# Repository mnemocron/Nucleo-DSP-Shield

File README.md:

# Nucleo-DSP-Shield
Audio DSP Shield for STM32 Nucleo-144 Boards (H723zg) based on the TLV320 CODEC

---

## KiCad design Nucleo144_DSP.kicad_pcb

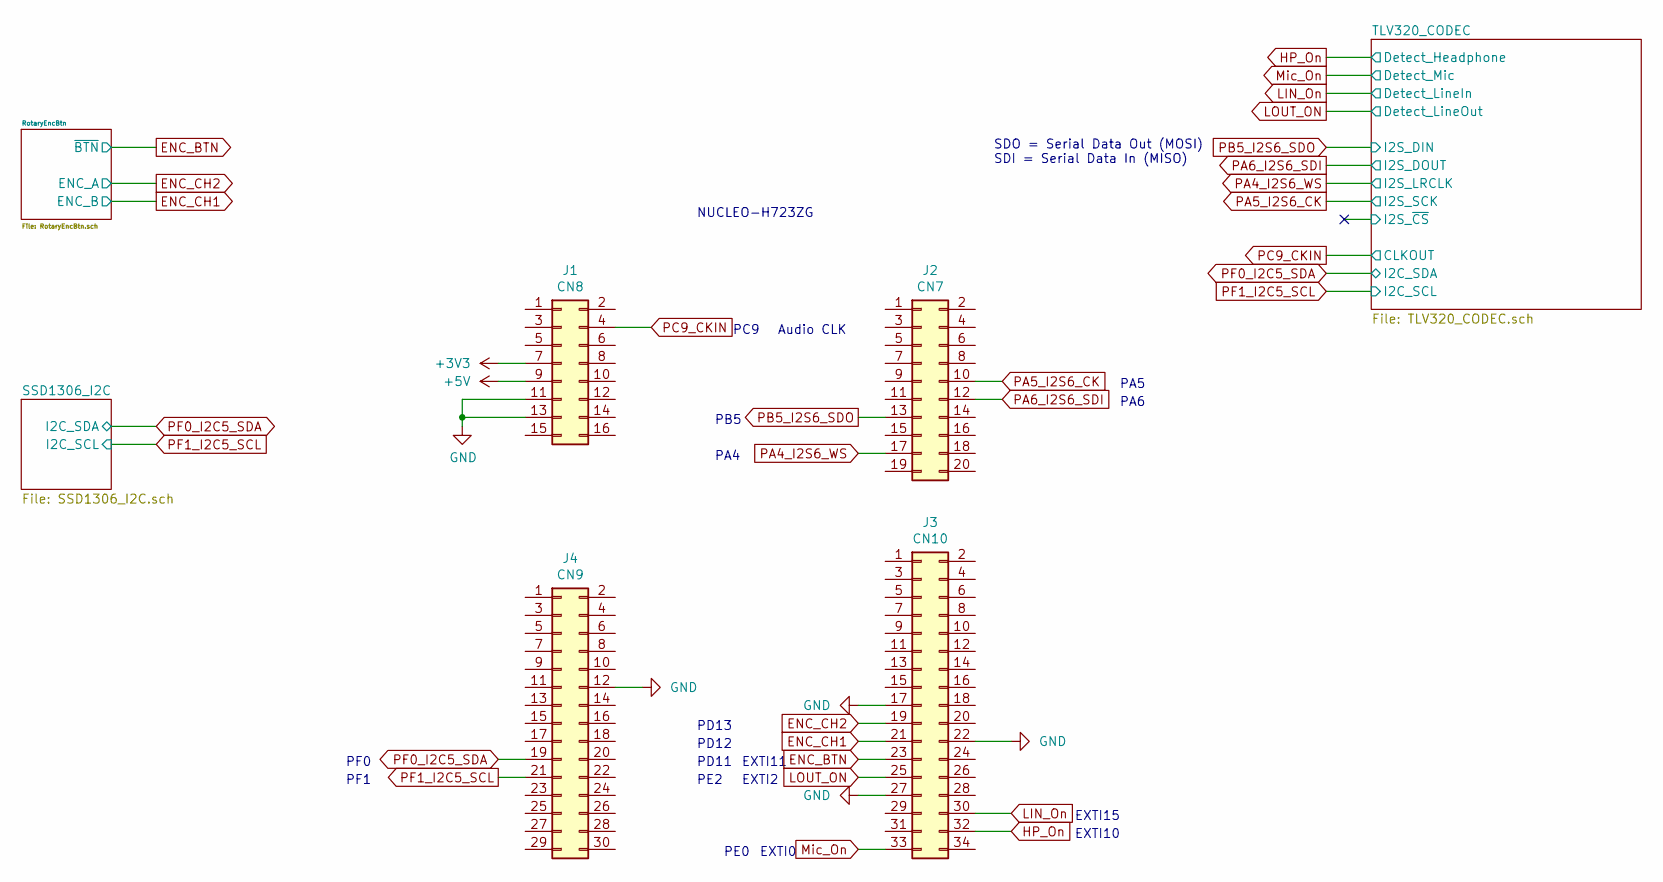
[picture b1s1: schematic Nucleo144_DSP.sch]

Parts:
J1: CN8; PinSocket_2x08_P2.54mm_Vertical; JLCPCB do not place
J2: CN7; PinSocket_2x10_P2.54mm_Vertical; JLCPCB do not place
J3: CN10; PinSocket_2x17_P2.54mm_Vertical; JLCPCB do not place
J4: CN9; PinSocket_2x15_P2.54mm_Vertical; JLCPCB do not place

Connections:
+5V: J1.9
ENC_BTN: J3.23; also elsewhere on the board
ENC_CH1: J3.21; also elsewhere on the board
ENC_CH2: J3.19; also elsewhere on the board
GND: J1.11, J1.13, J3.17, J3.22, J3.27, J4.12; also elsewhere on the board
HP_On: J3.32; also elsewhere on the board
LIN_On: J3.30; also elsewhere on the board
LOUT_ON: J3.25; also elsewhere on the board
Mic_On: J3.33; also elsewhere on the board
PA4_I2S6_WS: J2.17; also elsewhere on the board
PA5_I2S6_CK: J2.10; also elsewhere on the board
PA6_I2S6_SDI: J2.12; also elsewhere on the board
PB5_I2S6_SDO: J2.13; also elsewhere on the board
PC9_CKIN: J1.4; also elsewhere on the board
PF0_I2C5_SDA: J4.19; also elsewhere on the board
PF1_I2C5_SCL: J4.21; also elsewhere on the board

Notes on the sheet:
NUCLEO-H723ZG
EXTI0
EXTI10
EXTI11
EXTI2
EXTI15
PE0
PE2
PD11
PD12
PD13
PA4
PB5
PA6
PA5
SDO = Serial Data Out (MOSI) SDI = Serial Data In (MISO)
PF1
PF0
PC9
Audio CLK

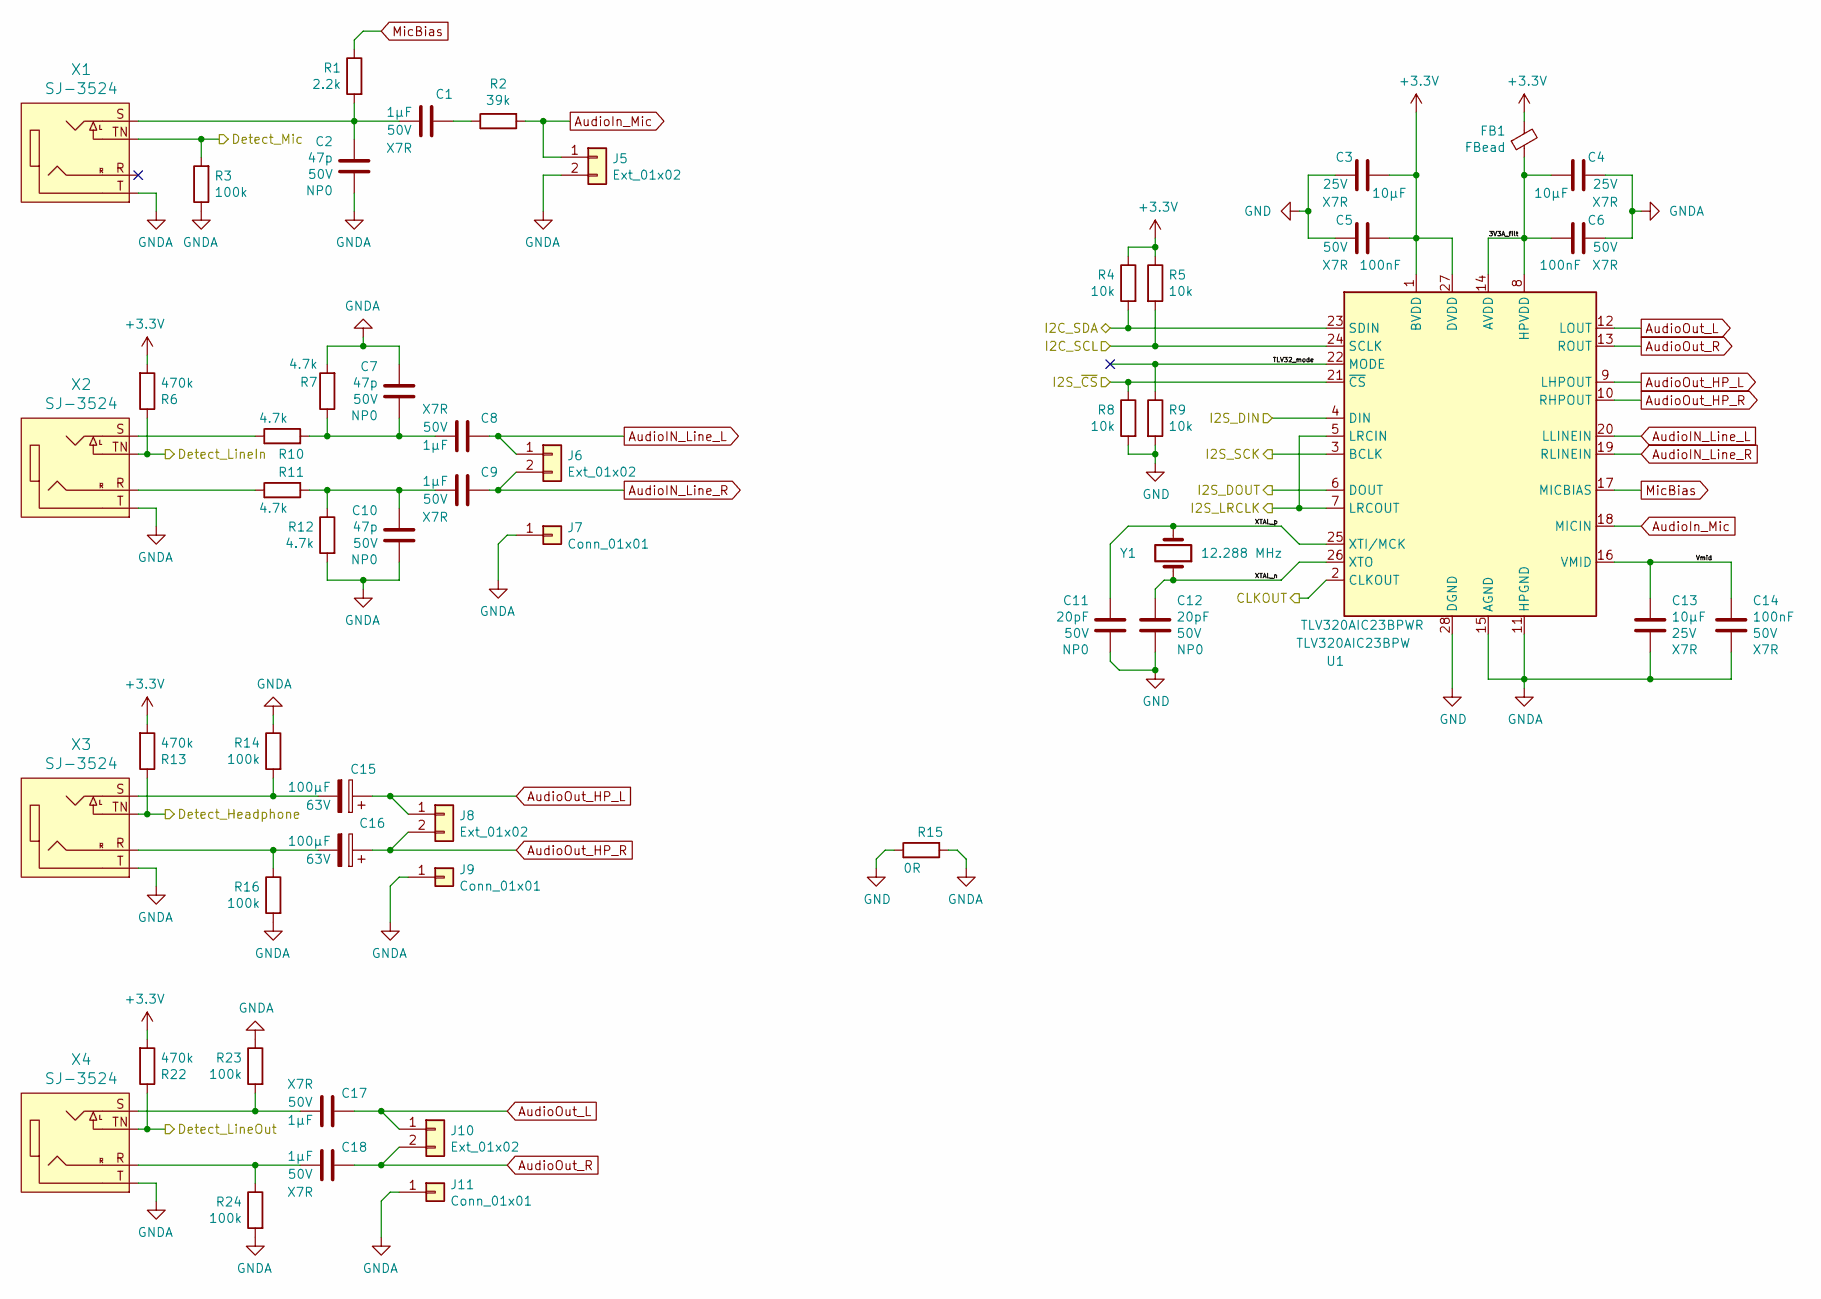
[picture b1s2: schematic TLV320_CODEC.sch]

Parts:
C1, C8, C9, C17, C18: 1μF; C_0805_2012Metric; Voltage 50V; JLCPCB Basic Part
C2, C7, C10: 47p; C_0805_2012Metric; Voltage 50V; JLCPCB Basic Part
C3, C4, C13: 10μF; C_0805_2012Metric; Voltage 25V; JLCPCB Basic Part
C5, C6, C14: 100nF; C_0805_2012Metric; Voltage 50V; JLCPCB Basic Part
C11, C12: 20pF; C_0805_2012Metric; Voltage 50V; JLCPCB Basic Part
C15, C16: 100μF; CP_Radial_D10.0mm_P5.00mm; Voltage 63V; JLCPCB do not place
FB1: FBead; R_0805_2012Metric; JLCPCB do not place
J5, J6, J8, J10: Ext_01x02; PinSocket_1x02_P2.54mm_Vertical; JLCPCB do not place
J7, J9, J11: Conn_01x01; PinSocket_1x01_P2.54mm_Vertical; JLCPCB do not place
R1: 2.2k; R_0805; Tolerance 1%; JLCPCB Basic Part
R2: 39k; R_0805; Tolerance 1%; JLCPCB Basic Part
R3, R14, R16, R23, R24: 100k; R_0805; Tolerance 1%; JLCPCB Basic Part
R4, R5, R8, R9: 10k; R_0805; Tolerance 1%; JLCPCB Basic Part
R6, R13, R22: 470k; R_0805; Tolerance 1%; JLCPCB Basic Part
R7, R10, R11, R12: 4.7k; R_0805; Tolerance 1%; JLCPCB Basic Part
R15: 0R; R_0805; Tolerance 1%; JLCPCB Basic Part
U1: TLV320AIC23BPW; TSSOP-28_4.4x9.7mm_P0.65mm; JLCPCB Extended Part
X1, X2, X3, X4: SJ-3524; Jack_3.5mm_CUI_SJ-3524-SMT_Horizontal; JLCPCB do not place
Y1: 12.288 MHz; Crystal_SMD_HC49-SD; JLCPCB Extended Part

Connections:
/TLV320_CODEC/3V3A_filt: C4.2, C6.2, FB1.1, U1.8 (HPVDD), U1.14 (AVDD)
/TLV320_CODEC/I2S_~CS~: R8.1, U1.21 (~CS~)
/TLV320_CODEC/TLV32_mode: R9.1, U1.22 (MODE)
/TLV320_CODEC/Vmid: C13.1, C14.1, U1.16 (VMID)
/TLV320_CODEC/XTAL_n: C12.2, U1.26 (XTO), Y1.1
/TLV320_CODEC/XTAL_p: C11.2, U1.25 (XTI/MCK), Y1.2
AudioIN_Line_L: C8.2, J6.1, U1.20 (LLINEIN)
AudioIN_Line_R: C9.2, J6.2, U1.19 (RLINEIN)
AudioIn_Mic: J5.1, R2.2, U1.18 (MICIN)
AudioOut_HP_L: C15.1, J8.1, U1.9 (LHPOUT)
AudioOut_HP_R: C16.1, J8.2, U1.10 (RHPOUT)
AudioOut_L: C17.2, J10.1, U1.12 (LOUT)
AudioOut_R: C18.2, J10.2, U1.13 (ROUT)
GND: C3.1, C5.1, C11.1, C12.1, R8.2, R9.2, R15.1, U1.28 (DGND); also elsewhere on the board
GNDA: C2.2, C4.1, C6.1, C7.1, C10.2, C13.2, C14.2, J5.2, J7.1, J9.1, J11.1, R3.1, R7.2, R12.2, R14.1, R15.2, R16.2, R23.1, R24.2, U1.11 (HPGND), U1.15 (AGND), X1.T, X2.T, X3.T, X4.T
HP_On: R13.1, X3.TN; also elsewhere on the board
LIN_On: R6.1, X2.TN; also elsewhere on the board
LOUT_ON: R22.1, X4.TN; also elsewhere on the board
MicBias: R1.1, U1.17 (MICBIAS)
Mic_On: R3.2, X1.TN; also elsewhere on the board
unnamed: C1.1, C2.1, R1.2, X1.S
unnamed: C1.2, R2.1
unnamed: C7.2, C8.1, R7.1, R10.2
unnamed: C9.1, C10.1, R11.2, R12.1
unnamed: C15.2, R14.2, X3.S
unnamed: C16.2, R16.1, X3.R
unnamed: C17.1, R23.2, X4.S
unnamed: C18.1, R24.1, X4.R
unnamed: R10.1, X2.S
unnamed: R11.1, X2.R
PA4_I2S6_WS: U1.5 (LRCIN), U1.7 (LRCOUT); also elsewhere on the board
PA5_I2S6_CK: U1.3 (BCLK); also elsewhere on the board
PA6_I2S6_SDI: U1.6 (DOUT); also elsewhere on the board
PB5_I2S6_SDO: U1.4 (DIN); also elsewhere on the board
PC9_CKIN: U1.2 (CLKOUT); also elsewhere on the board
PF0_I2C5_SDA: R4.2, U1.23 (SDIN); also elsewhere on the board
PF1_I2C5_SCL: R5.2, U1.24 (SCLK); also elsewhere on the board

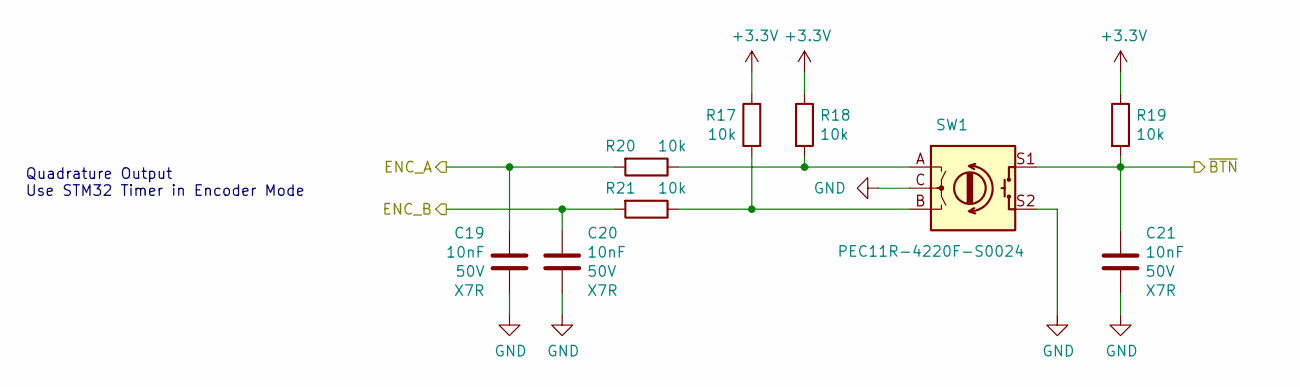
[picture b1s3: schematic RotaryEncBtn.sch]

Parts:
C19, C20, C21: 10nF; C_0805_2012Metric; Voltage 50V; JLCPCB Basic Part
R17, R18, R19, R20, R21: 10k; R_0805; Tolerance 1%; JLCPCB Basic Part
SW1: PEC11R-4220F-S0024; RotaryEncoder_Alps_EC11E-Switch_Vertical_H20mm_CircularMoun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; JLCPCB do not place

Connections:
ENC_BTN: C21.1, R19.2, SW1.S1; also elsewhere on the board
ENC_CH1: C20.1, R21.2; also elsewhere on the board
ENC_CH2: C19.2, R20.2; also elsewhere on the board
GND: C19.1, C20.2, C21.2, SW1.C, SW1.S2; also elsewhere on the board
unnamed: R17.2, R21.1, SW1.B
unnamed: R18.2, R20.1, SW1.A

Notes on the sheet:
Quadrature Output Use STM32 Timer in Encoder Mode

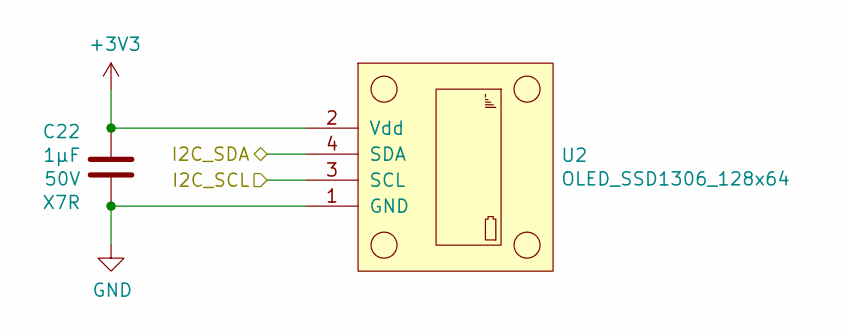
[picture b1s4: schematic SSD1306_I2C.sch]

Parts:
C22: 1μF; C_0805_2012Metric; Voltage 50V; JLCPCB Basic Part
U2: OLED_SSD1306_128x64; PinSocket_1x04_P2.54mm_Vertical; JLCPCB do not place

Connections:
GND: C22.1, U2.1 (GND); also elsewhere on the board
PF0_I2C5_SDA: U2.4 (SDA); also elsewhere on the board
PF1_I2C5_SCL: U2.3 (SCL); also elsewhere on the board

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
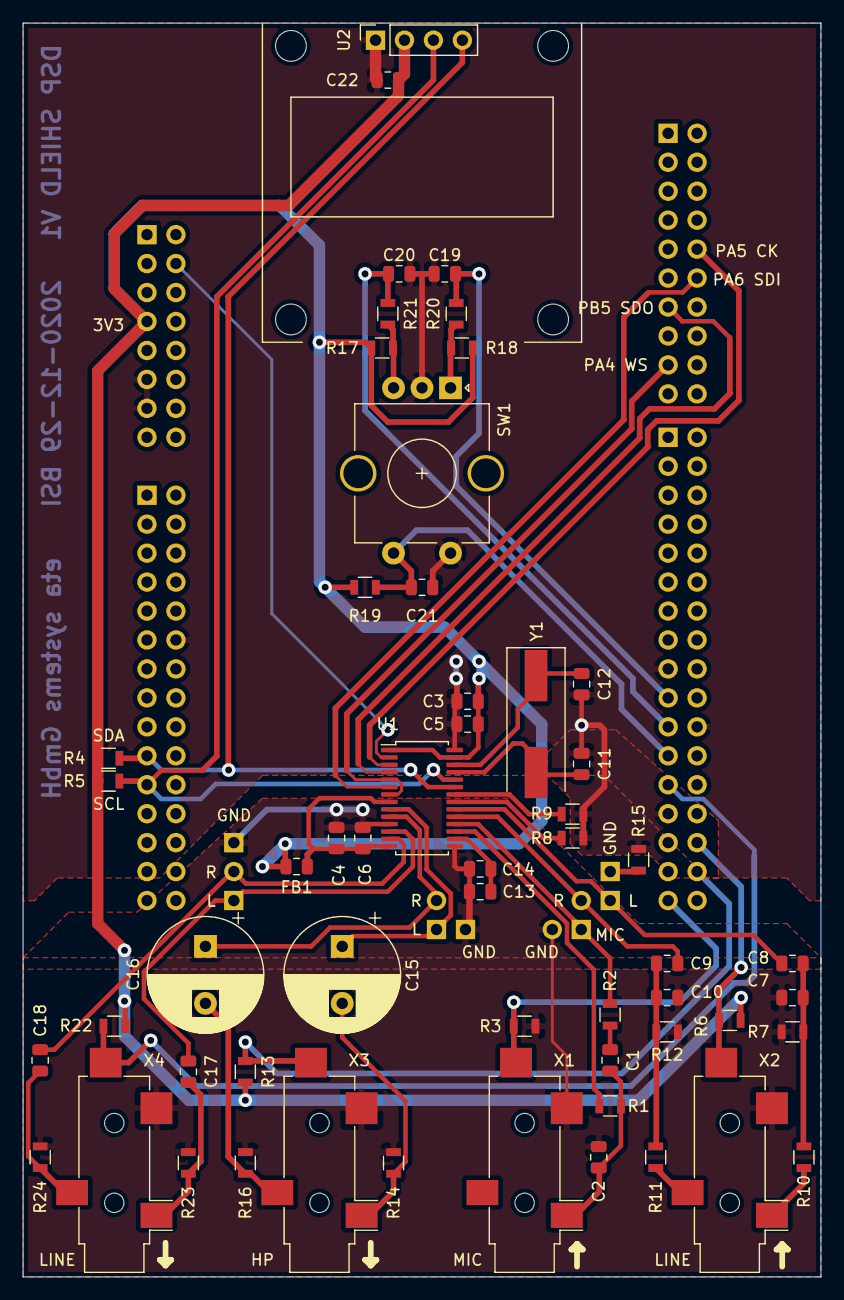
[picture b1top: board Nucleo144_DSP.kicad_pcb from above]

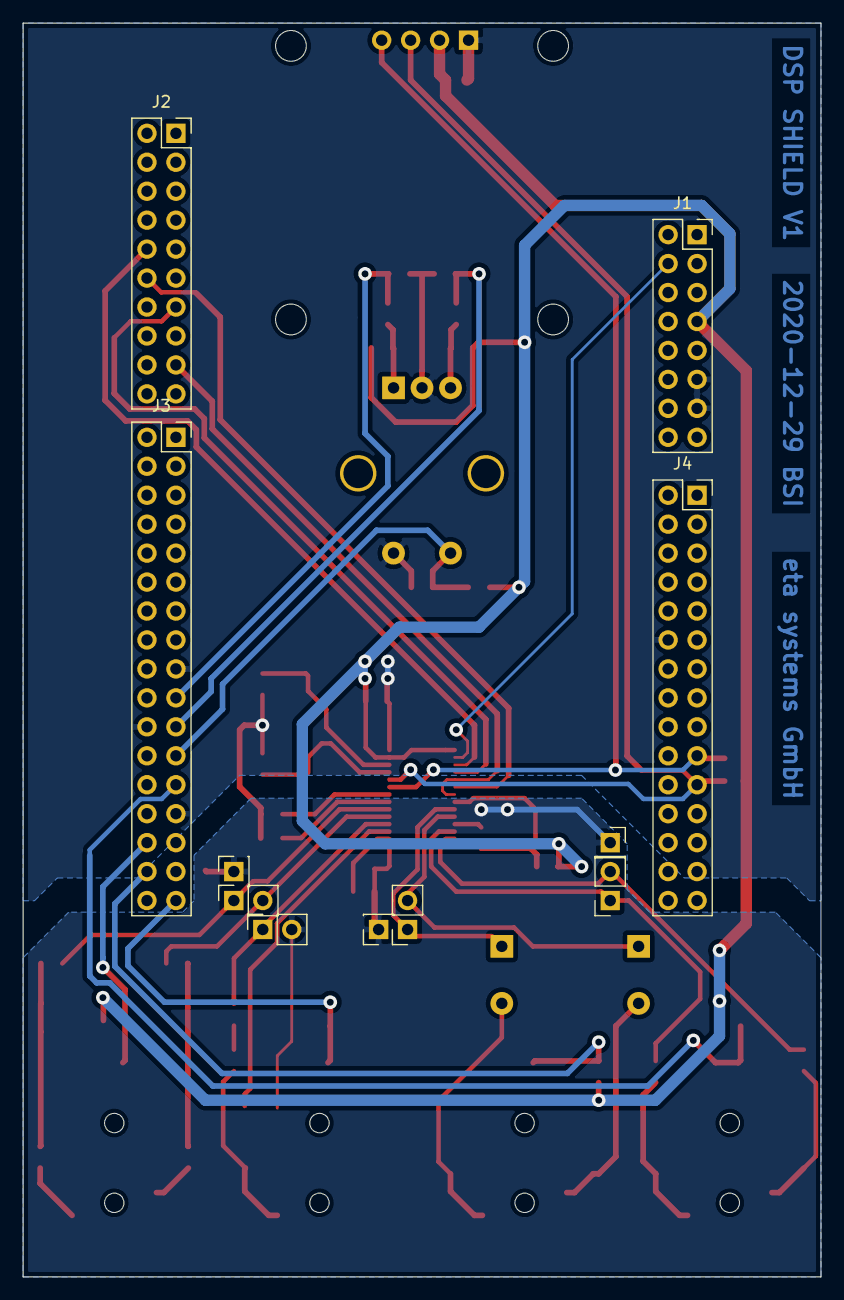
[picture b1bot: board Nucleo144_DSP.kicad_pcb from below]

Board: 2 copper layers, 70.0 x 110.0 mm, 66 parts (11 on the bottom side), 43 nets.

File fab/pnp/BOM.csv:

Designator,Value,Footprint,Article,Comment,JLC Part Type,Manufacturer,Power,Tolerance,Type,Voltage,Price @ JLC,QTY
" C2, C7, C10",47p,805,CL21C470JBANNNC,MULTILAYER CERAMIC CAPACITORS MLCC - SMD/SMT 47PF 50V 0805 ROHS,Basic Part,Samsung,-,-,NP0,50V,0.0112,3
C2,47p,805,CL21C470JBANNNC,MULTILAYER CERAMIC CAPACITORS MLCC - SMD/SMT 47PF 50V 0805 ROHS,Basic Part,Samsung,-,-,NP0,50V,0.0112,1
C7,47p,805,CL21C470JBANNNC,MULTILAYER CERAMIC CAPACITORS MLCC - SMD/SMT 47PF 50V 0805 ROHS,Basic Part,Samsung,-,-,NP0,50V,0.0112,1
C10,47p,805,CL21C470JBANNNC,MULTILAYER CERAMIC CAPACITORS MLCC - SMD/SMT 47PF 50V 0805 ROHS,Basic Part,Samsung,-,-,NP0,50V,0.0112,1
" C11, C12",20pF,805,CL21C200JBANNNC,MULTILAYER CERAMIC CAPACITORS MLCC - SMD/SMT 20PF 50V 0805 ROHS,Basic Part,Samsung,-,-,NP0,50V,0.0112,2
"C3, C4, C13",10uF,805,CL21A106KAYNNNE,MULTILAYER CERAMIC CAPACITORS MLCC - SMD/SMT 10UF 25V 0805 ROHS,Basic Part,Samsung,-,-,X7R,25V,0.0259,3
"C5, C6, C14",100nF,805,CC0805KRX7R9BB104,MULTILAYER CERAMIC CAPACITORS MLCC - SMD/SMT 100NF 50V 0805 ROHS,Basic Part,Yageo,-,-,X7R,50V,0.001,3
"C15, C16",100uF,,EEU-FC1J101,-,do not place,Panasonic,-,-,-,63V,-,2
"C1, C8, C9, C17, C18, C22",1uF,805,CL21B105KBFNNNE,MULTILAYER CERAMIC CAPACITORS MLCC - SMD/SMT 1UF 50V 0805 ROHS,Basic Part,Samsung,-,-,X7R,50V,0.0186,6
"C19, C20, C21",10nF,805,CL21B103KBANNNC,MULTILAYER CERAMIC CAPACITORS MLCC - SMD/SMT 10NF 50V 0805 ROHS,Basic Part,Samsung,-,-,X7R,50V,0.001,3
FB1,FBead,805,do not place,-,do not place,Wuerth Electronics,-,-,-,-,-,1
"J1,CN8",,do not place,-,do not place,-,-,-,-,-,-,1,
"J2,CN7",,do not place,-,do not place,-,-,-,-,-,-,1,
"J3,CN10",,do not place,-,do not place,-,-,-,-,-,-,1,
"J4,CN9",,do not place,-,do not place,-,-,-,-,-,-,1,
"J5, J6, J8, J10",Ext_01x02,,do not place,-,do not place,-,-,-,-,-,-,4
"J7, J9, J11",Conn_01x01,,do not place,-,do not place,-,-,-,-,-,-,3
"R1,2.2k",805,0805W8F2201T5E,CHIP RESISTOR - SURFACE MOUNT 2.2KOHMS ±1% 1/8W 0805 ROHS,Basic Part,-,1/8 W,1%,-,-,0.0033,1,
"R2,39k",805,0805W8F3902T5E,CHIP RESISTOR - SURFACE MOUNT 39KOHMS ±1% 1/8W 0805 ROHS,Basic Part,-,1/8 W,1%,-,-,0.0034,1,
"R4, R5, R8, R9, R17-R21",10k,805,0805W8F1002T5E,CHIP RESISTOR - SURFACE MOUNT 10KOHMS ±1% 1/8W 0805 ROHS,Basic Part,-,1/8 W,1%,-,-,0.0035,9
"R7, R10-R12",4.7k,805,0805W8F4701T5E,CHIP RESISTOR - SURFACE MOUNT 4.7KOHMS ±1% 1/8W 0805 ROHS,Basic Part,-,1/8 W,1%,-,-,0.0034,4
"R6, R13, R22",470k,805,0805W8F4703T5E,CHIP RESISTOR - SURFACE MOUNT 470KOHMS ±1% 1/8W 0805 ROHS,Basic Part,-,1/8 W,1%,-,-,0.0034,3
"R3, R14, R16, R23, R24",100k,805,0805W8F1003T5E,CHIP RESISTOR - SURFACE MOUNT 100KOHMS ±1% 1/8W 0805 ROHS,Basic Part,-,1/8 W,1%,-,-,0.0034,5
R15,0R,805,0805W8F0000T5E,CHIP RESISTOR - SURFACE MOUNT 0OHMS ±1% 1/8W 0805 ROHS,Basic Part,-,1/8 W,1%,-,-,0.0035,1
SW1,PEC11R-4220F-S0024,,PEC11R-4220F-S0024,-,do not place,-,-,-,-,-,-,1
U1,TLV320AIC23BPW,TSSOP-28,TLV320AIC23BPWR,VIDEO-AUDIO INTERFACE ICS TSSOP-28 ROHS,Extended Part,Texas Instruments,-,-,-,-,1.545,1
U2,OLED_SSD1306_128x64,,do not place,-,do not place,-,-,-,-,-,-,1
"X1, X2, X3, X4",SJ-3524,,SJ-3524-SMT-TR,-,do not place,-,-,-,-,-,-,4
Y1,12.288 MHz,HC49-SD,6CS12288F20UCG,12.288MHZ ±20PPM 20PF 40? HC-49SMD SMD CRYSTAL RESONATORS ROHS,Extended Part,-,-,-,-,-,0.0974,1

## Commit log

2021-01-03 v1.0
